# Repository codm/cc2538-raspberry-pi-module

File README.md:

# cod.m ZigBee CC2538 Raspberry Pi module
[ZigBee CC2538 Raspberry Pi Coordinator](https://shop.codm.de/automation/zigbee/29/zigbee-cc2538-raspberry-pi-modul) - a ZigBee Coordinator designed for the GPIO of the Raspberry Pi running Z-Stack Firmware 3.0.x.
The used CC2538 module has an onboard CC2592 PA/LNA for range extension. Together with an external antenna this should make - depending on your surrounding - for a very good coverage.

According to [koenkk](https://github.com/Koenkk/Z-Stack-firmware/tree/master/coordinator) the CC2538 allows for up to 100 direct children and 200/400 routes directly on the coordinator. Keep in mind that the size of a ZigBee mesh is not defined by the count of possible direct children at the coordinator, see https://www.zigbee2mqtt.io/information/FAQ.html#i-read-that-zigbee2mqtt-has-a-limit-of-20-devices-is-this-true

If you are interessted in the development of the module, take a look here: https://github.com/Koenkk/zigbee2mqtt/issues/1568#issuecomment-670571253

The corresponding eagle library for the CC2538 module, including 3D model (thanks to @co-Palko), can be found here: https://github.com/codm/eagle-libraries

You can buy a ready built coordinator, including external antenna at our webshop: https://shop.codm.de/automation/zigbee/29/zigbee-cc2538-raspberry-pi-modul

# Running
To us the module directly on the serial interface on the GPIO of the Raspberry Pi, you have to free it up first. Either completely or by moving the Bluetooth UART to the mini-uart.

See  https://www.raspberrypi.org/documentation/configuration/uart.md
Also explained in the manual (german): [Anleitung cod.m ZigBee CC2538 Raspberry Pi Modul](https://shop.codm.de/media/pdf/3f/e7/be/20200901_ZigBee_CC2538_Raspberry_Pi_Modul_V03_Datenblatt_Anleitung-codm.pdf) 

# Antenna
We recommend to use only external antennas as the module is close to the WiFi and Bluetooth module/antenna on the Raspberry Pi. But if you want to use the attached PCB antenna, rotate the resistor pointing to the u.FL socket by 90° so it connects the PCB trace.

Well, that's a feature of the used CC2538 module 😉

# Firmware
The firmware is the same used on the modkam module, but adapted for direct UART use by @reverieline: https://github.com/reverieline/CC2538-CC2592-ZNP/

You can flash the firmware either by JTAG or directly from the Raspberry Pi using [cc2538-prog](https://github.com/1248/cc2538-prog/). 
Keep in mind, you have to flash a firmware with a serial bootloader (SBL) to use this feature again, e.g. `MODKAMRU_V3_UART-no-flow-control_with_SBL.hex`.

## JTAG
The 2x05 header is following the common [JTAG-Cortex-M0](https://www.segger.com/products/debug-probes/j-link/accessories/adapters/9-pin-cortex-m-adapter/) Layout.

The original adapter for the "normal" 20-pin JTAG layout is quite expensive, so we've built our own. You'll find alternatives around the web or get in touch with us.

## Serial via GPIO
Install and compile [cc2538-prog](https://github.com/1248/cc2538-prog/).

While connected and powered through the Pi, hold down the `flash` button on the module and press `reset` shortly while still holding `flash`. The CC2538 should now be in the bootloder.

Then execute `./cc2538-prog -d /dev/ttyAMA0 -f MODKAMRU_V3_UART-no-flow-control_with_SBL.hex`

The output should look like this: 
```
ping ok
Bootloader detected
Erasing page 0
Erasing page 1
[...]
Erasing page 254
Erasing page 255
Writing 16 bytes to 0x00200000
Writing 16 bytes to 0x00200010
[...]
Writing 16 bytes to 0x0023C7F0
Writing 12 bytes to 0x0027FFD4
```

After that reset the module using the corresponding button. 
It happened sometimes that I had to replug the module to get it to work again. 

# Thanks
* @koenkk Z-Stack Firmware - https://github.com/Koenkk/Z-Stack-firmware
* @reverieline UART Version of the Z-Stack firmware - https://github.com/reverieline/CC2538-CC2592-ZNP/tree/master/MODKAMRU_V3
* @co-Palko 3D model of the chinese module - https://github.com/co-Palko
* @1248 cc2538-prog - https://github.com/1248/cc2538-prog/

# License
[CC-BY-SA 3.0](https://creativecommons.org/licenses/by-sa/3.0/)

cod.m GmbH, Patrik Mayer, 2020

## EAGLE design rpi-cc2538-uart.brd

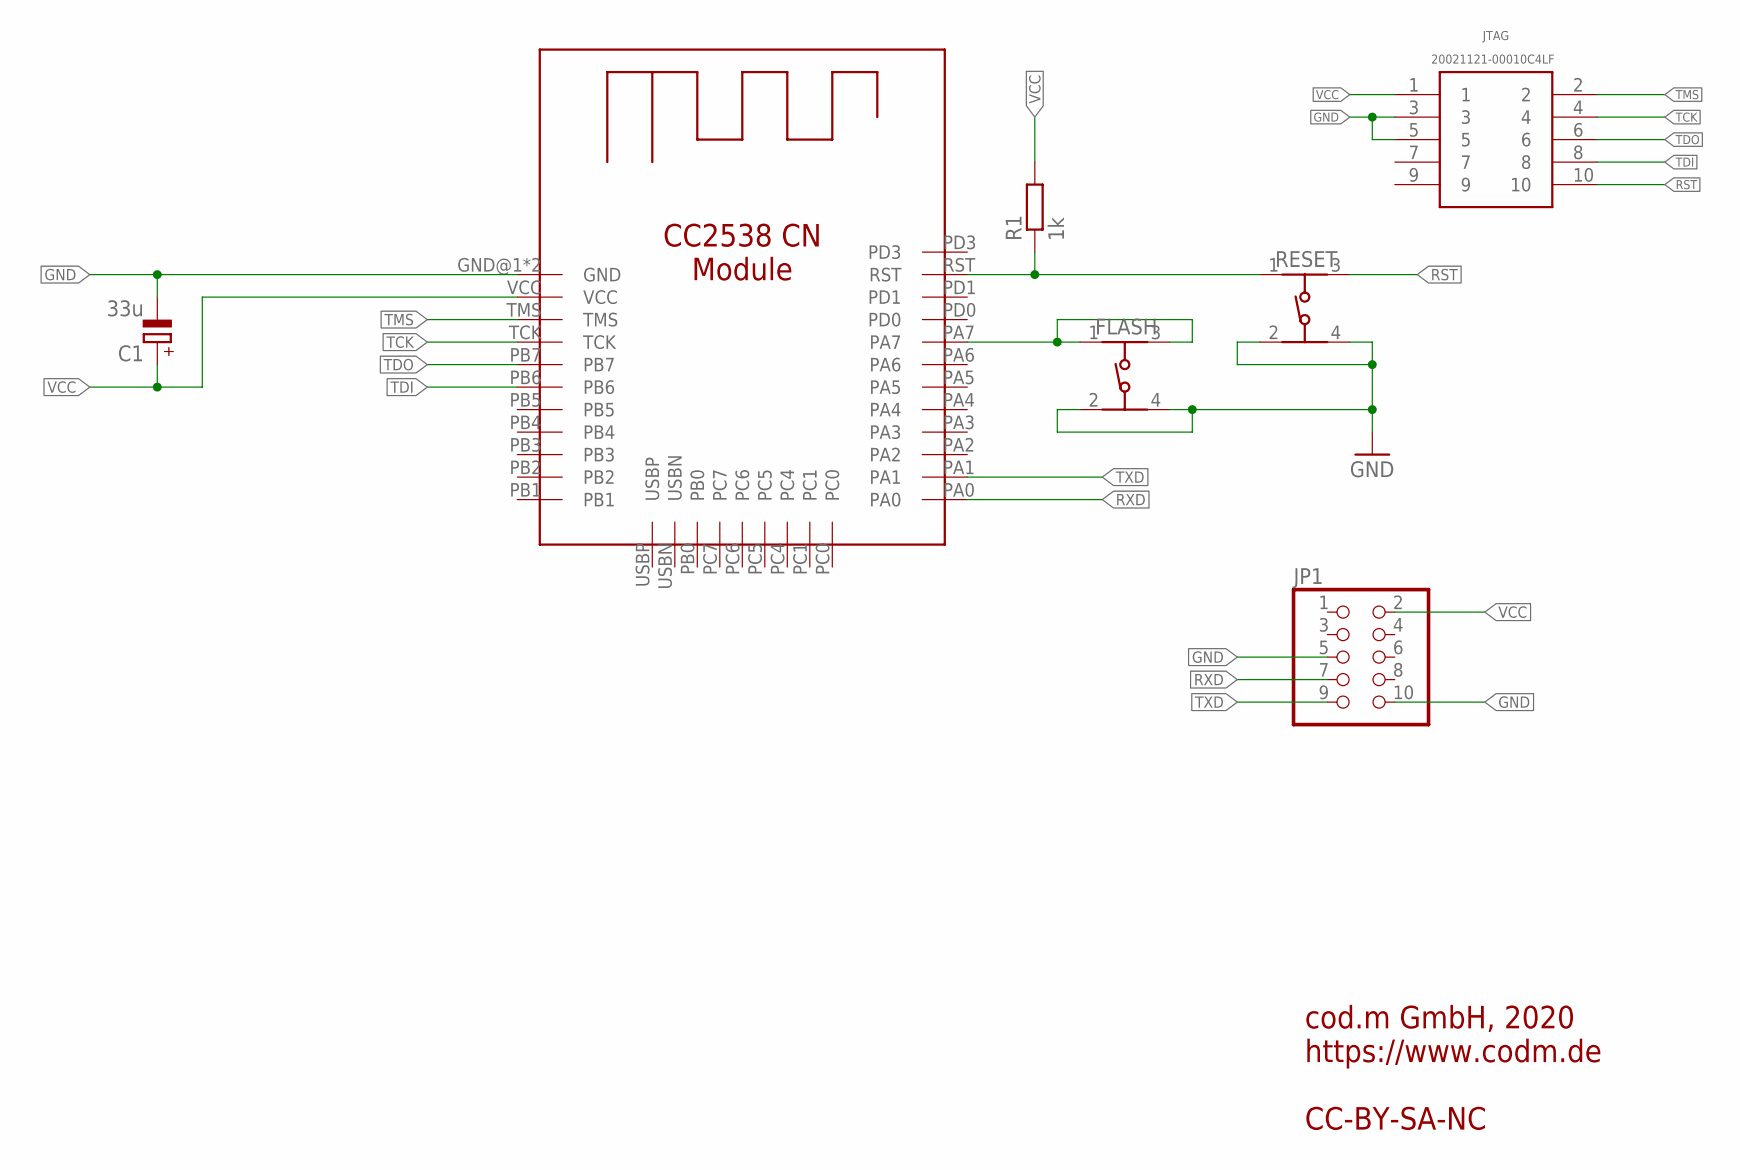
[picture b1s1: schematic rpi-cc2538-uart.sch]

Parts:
C1: 33u; A/3216-18W
FLASH: 434153017835
JP1: PINHD-2X5; 2X05
JTAG: 20021121-00010C4LF; 2002112100010C4LF
R1: 1k; R0805
RESET: 434153017835
U$1: CC2538-CN

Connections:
FLASH: FLASH.1, FLASH.3 (2), U$1.PA7
GND: C1.-, FLASH.2 (3), FLASH.4, JP1.5, JP1.10, JTAG.3, JTAG.5, RESET.2 (3), RESET.4, U$1.GND@1 (GND), U$1.GND@2 (GND)
RST: JTAG.10, R1.1, RESET.1, RESET.3 (2), U$1.RST
RXD: JP1.7, U$1.PA0
TCK: JTAG.4, U$1.TCK
TDI: JTAG.8, U$1.PB6
TDO: JTAG.6, U$1.PB7
TMS: JTAG.2, U$1.TMS
TXD: JP1.9, U$1.PA1
VCC: C1.+, JP1.2, JTAG.1, R1.2, U$1.VCC

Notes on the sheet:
cod.m GmbH, 2020 https://www.codm.de CC-BY-SA-NC

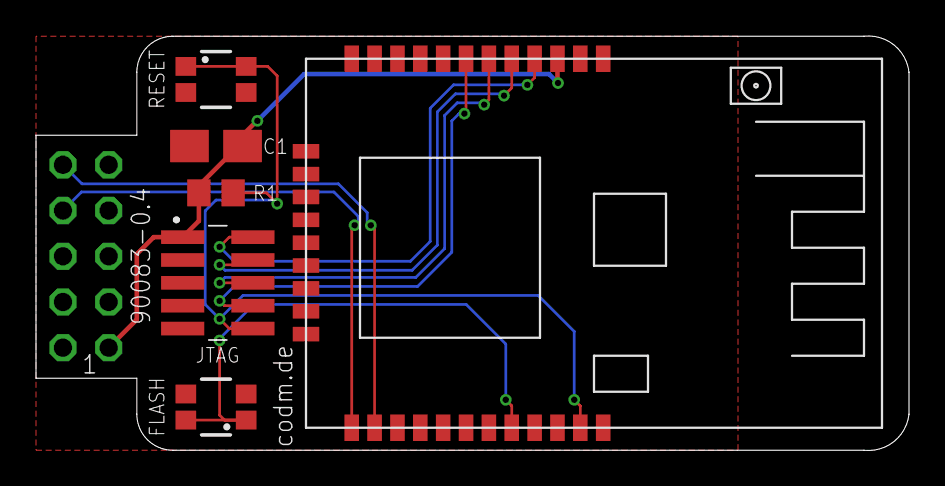
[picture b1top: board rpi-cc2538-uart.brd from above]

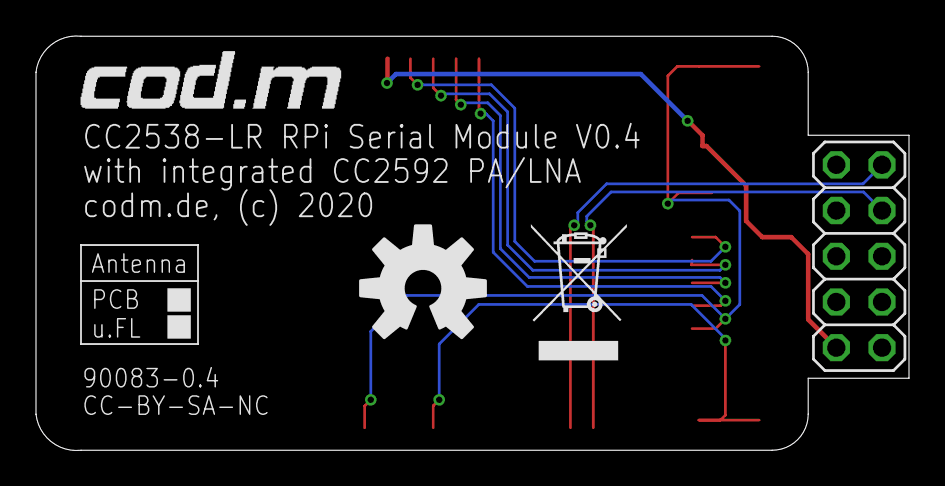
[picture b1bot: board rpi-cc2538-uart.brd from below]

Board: 2 copper layers, 48.5 x 23.0 mm, 10 parts (4 on the bottom side), 10 nets.

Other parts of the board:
U$2: CODM-LOGO
U$3: WEEE-LOGO-5MM
U$4: OSHW-LOGO-L

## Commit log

2020-09-08 first public release
2020-09-08 refined readme
2020-09-08 moved license to CC-BY-SA
2020-11-13 minor changes for new aisler dru
2020-12-09 cc2538 footprint with larger pads, refined groundplane

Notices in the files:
rpi-cc2538-uart.brd:
codm.de, (c) 2020
parts and their libraries:
SparkFun-Aesthetics: Licensing: Creative Commons ShareAlike 4.0 International - https://creativecommons.org/licenses/by-sa/4.0
434153017835_Eagle_WS-TASV_rev20a: Copyright: Würth Elektronik
